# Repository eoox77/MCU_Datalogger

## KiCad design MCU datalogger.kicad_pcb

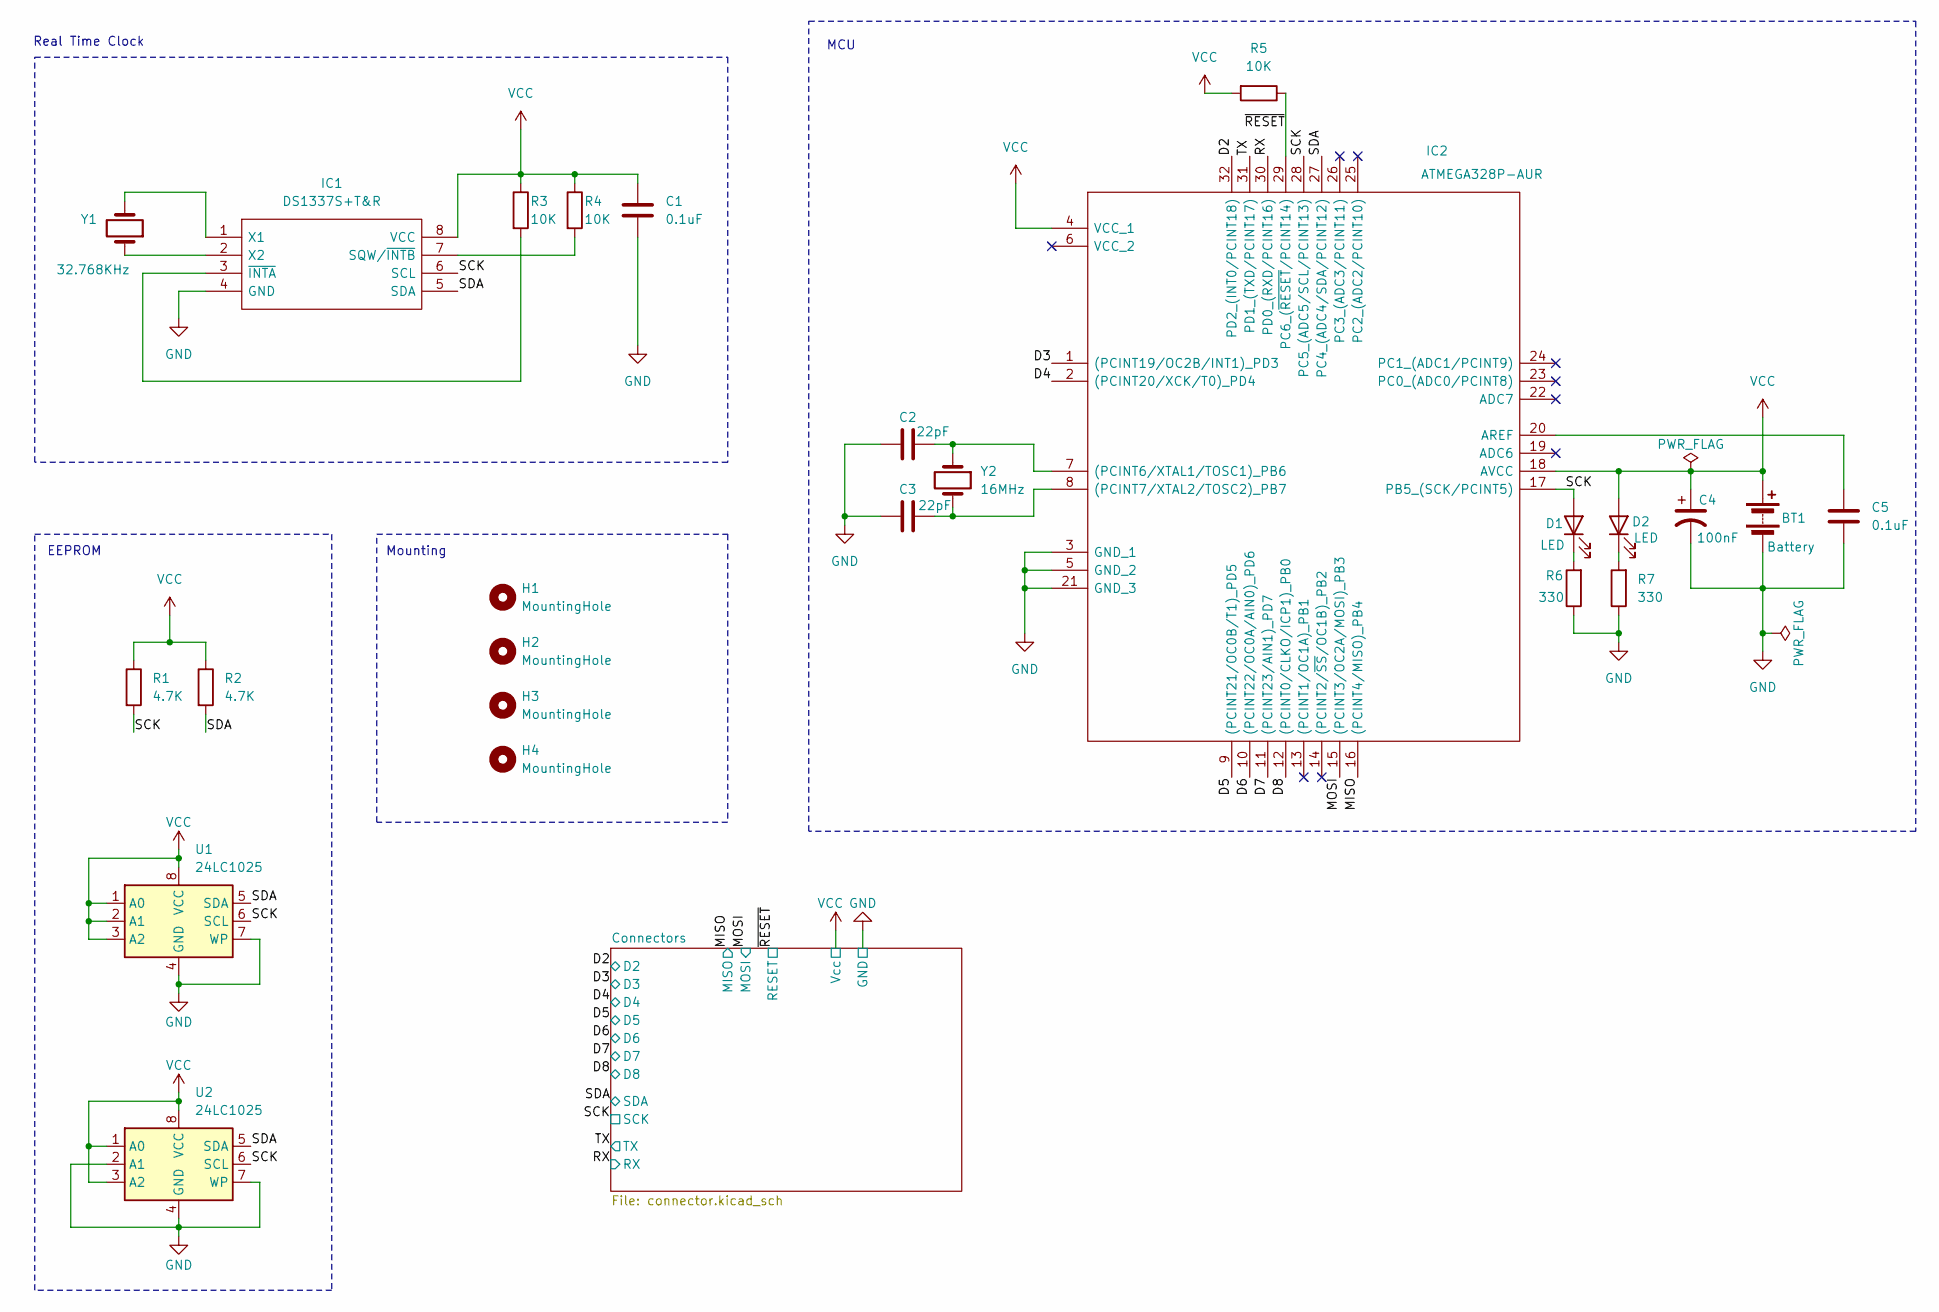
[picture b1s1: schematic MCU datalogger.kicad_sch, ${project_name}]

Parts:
BT1: Battery; PinHeader_1x02_P2.54mm_Vertical
C1, C5: 0.1uF; C_0805_2012Metric
C2, C3: 22pF; C_0805_2012Metric
C4: 100nF; C_0805_2012Metric
D1, D2: LED; LED_0805_2012Metric
H1, H2, H3, H4: MountingHole; MountingHole_2.1mm
IC1: DS1337S+T&R; SOIC127P600X175-8N; Manufacturer_Part_Number DS1337S+T&R; Mouser Part Number 700-DS1337ST&R
IC2: ATMEGA328P-AUR; QFP80P900X900X120-32N; Manufacturer_Part_Number ATMEGA328P-AUR; Mouser Part Number 556-ATMEGA328P-AUR
R1, R2: 4.7K; R_0805_2012Metric
R3, R4, R5: 10K; R_0805_2012Metric
R6, R7: 330; R_0805_2012Metric
U1, U2: 24LC1025; SOIC-8_5.23x5.23mm_P1.27mm
Y1: 32.768KHz; Crystal_SMD_5032-2Pin_5.0x3.2mm
Y2: 16MHz; Crystal_SMD_5032-2Pin_5.0x3.2mm

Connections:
/D2: IC2.32 (PD2_(INT0/PCINT18)); also elsewhere on the board
/D3: IC2.1 ((PCINT19/OC2B/INT1)_PD3); also elsewhere on the board
/D4: IC2.2 ((PCINT20/XCK/T0)_PD4); also elsewhere on the board
/D5: IC2.9 ((PCINT21/OC0B/T1)_PD5); also elsewhere on the board
/D6: IC2.10 ((PCINT22/OC0A/AIN0)_PD6); also elsewhere on the board
/D7: IC2.11 ((PCINT23/AIN1)_PD7); also elsewhere on the board
/D8: IC2.12 ((PCINT0/CLKO/ICP1)_PB0); also elsewhere on the board
/MISO: IC2.16 ((PCINT4/MISO)_PB4); also elsewhere on the board
/MOSI: IC2.15 ((PCINT3/OC2A/MOSI)_PB3); also elsewhere on the board
/RX: IC2.30 (PD0_(RXD/PCINT16)); also elsewhere on the board
/SCK: D1.2 (A), IC1.6 (SCL), IC2.17 (PB5_(SCK/PCINT5)), IC2.28 (PC5_(ADC5/SCL/PCINT13)), R1.2, U1.6 (SCL), U2.6 (SCL); also elsewhere on the board
/SDA: IC1.5 (SDA), IC2.27 (PC4_(ADC4/SDA/PCINT12)), R2.2, U1.5 (SDA), U2.5 (SDA); also elsewhere on the board
/TX: IC2.31 (PD1_(TXD/PCINT17)); also elsewhere on the board
/~RESET: IC2.29 (PC6_(~RESET/PCINT14)), R5.1; also elsewhere on the board
GND: BT1.2 (-), C1.2, C2.1, C3.2, C4.2, C5.1, IC1.4 (GND), IC2.3 (GND_1), IC2.5 (GND_2), IC2.21 (GND_3), R6.1, R7.1, U1.4 (GND), U1.7 (WP), U2.2 (A1), U2.4 (GND), U2.7 (WP); also elsewhere on the board
unnamed: D1.1 (K), R6.2
unnamed: D2.1 (K), R7.2
unnamed: IC1.7 (SQW/~INTB), R4.2
unnamed: IC1.1 (X1), Y1.2
unnamed: IC1.2 (X2), Y1.1
unnamed: IC1.3 (~INTA), R3.2
unnamed: C2.2, IC2.7 ((PCINT6/XTAL1/TOSC1)_PB6), Y2.1
unnamed: C3.1, IC2.8 ((PCINT7/XTAL2/TOSC2)_PB7), Y2.2
unnamed: C5.2, IC2.20 (AREF)
VCC: BT1.1 (+), C1.1, C4.1, D2.2 (A), IC1.8 (VCC), IC2.4 (VCC_1), IC2.18 (AVCC), R1.1, R2.1, R3.1, R4.1, R5.2, U1.1 (A0), U1.2 (A1), U1.3 (A2), U1.8 (VCC), U2.1 (A0), U2.3 (A2), U2.8 (VCC); also elsewhere on the board

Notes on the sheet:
EEPROM
Mounting
MCU
Real Time Clock

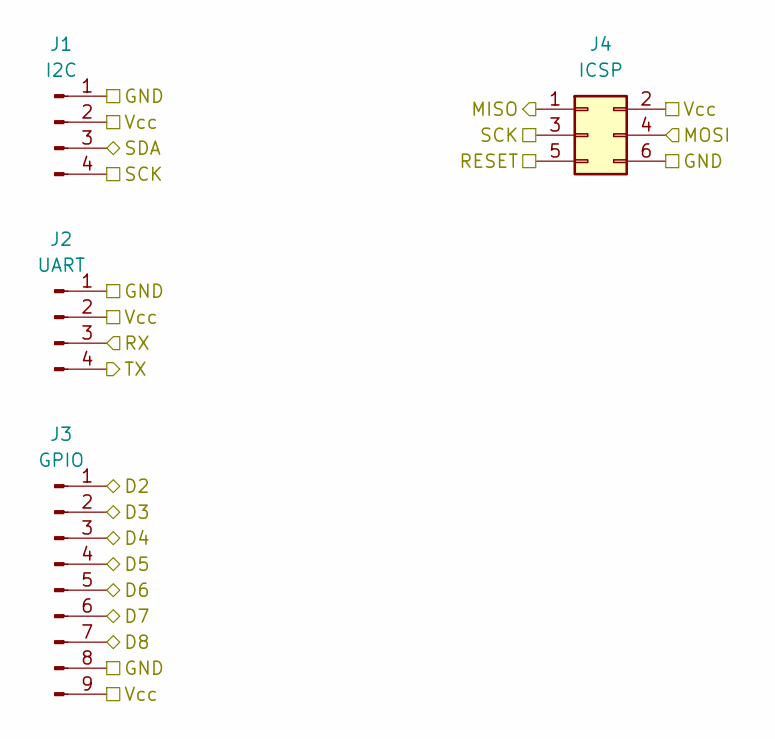
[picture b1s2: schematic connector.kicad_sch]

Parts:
J1: I2C; PinHeader_1x04_P2.54mm_Vertical
J2: UART; PinHeader_1x04_P2.54mm_Vertical
J3: GPIO; PinHeader_1x09_P2.54mm_Vertical
J4: ICSP; PinHeader_2x03_P2.54mm_Vertical

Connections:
/D2: J3.1; also elsewhere on the board
/D3: J3.2; also elsewhere on the board
/D4: J3.3; also elsewhere on the board
/D5: J3.4; also elsewhere on the board
/D6: J3.5; also elsewhere on the board
/D7: J3.6; also elsewhere on the board
/D8: J3.7; also elsewhere on the board
/MISO: J4.1; also elsewhere on the board
/MOSI: J4.4; also elsewhere on the board
/RX: J2.3; also elsewhere on the board
/SCK: J1.4, J4.3; also elsewhere on the board
/SDA: J1.3; also elsewhere on the board
/TX: J2.4; also elsewhere on the board
/~RESET: J4.5; also elsewhere on the board
GND: J1.1, J2.1, J3.8, J4.6; also elsewhere on the board
VCC: J1.2, J2.2, J3.9, J4.2; also elsewhere on the board

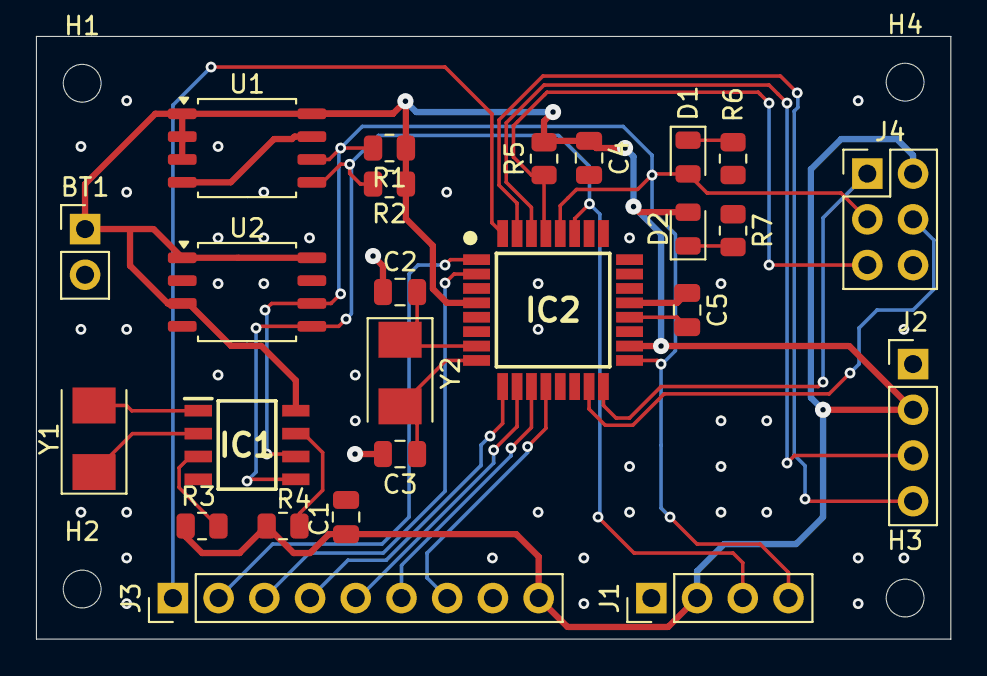
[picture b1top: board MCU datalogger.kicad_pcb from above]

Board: 2 copper layers, 50.8 x 33.5 mm, 29 parts (0 on the bottom side), 25 nets.

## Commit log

2024-12-20 First commit of new project
2024-12-23 add unit
2024-12-23 Completed wiring of main sheet.
2024-12-24 Complete wiring of second sheet
2024-12-24 Completed Comment.
2024-12-24 Setup PCB New.
2024-12-24 Complete Layout Line.
2024-12-27 Complete 2 Layer PCB
2024-12-27 add gerber folder
